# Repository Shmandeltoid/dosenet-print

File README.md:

# dosenet-print
for 3D print and PCB design files

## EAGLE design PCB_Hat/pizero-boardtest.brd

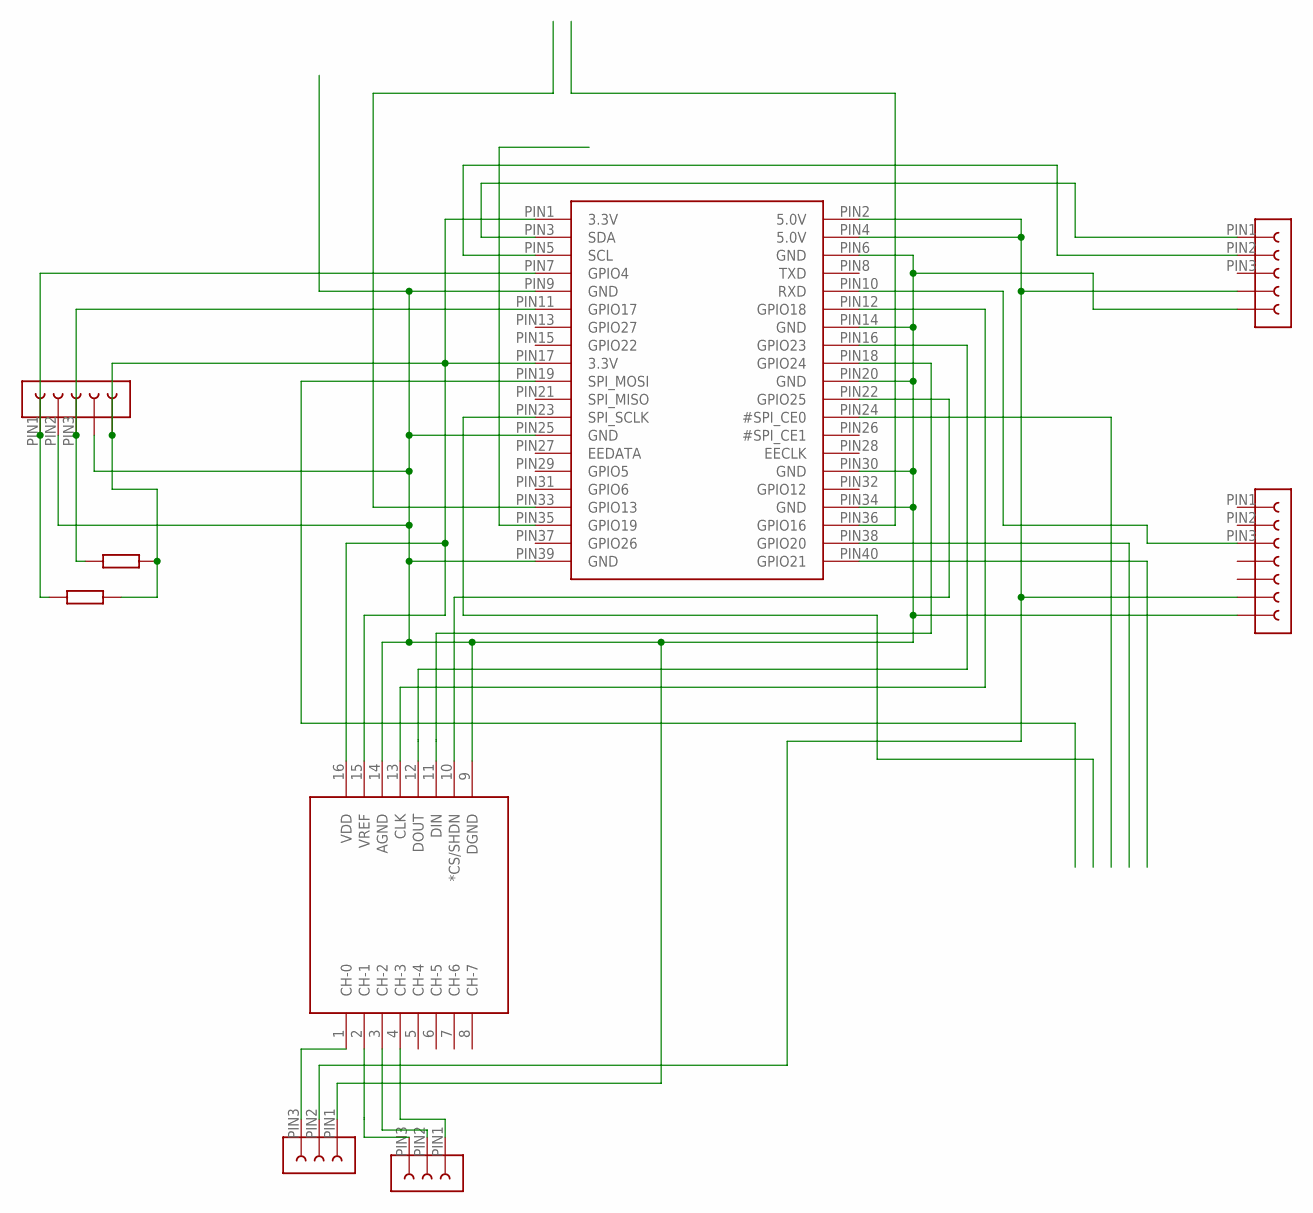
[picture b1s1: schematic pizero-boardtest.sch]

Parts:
ADC: ADC-CHIP; MCP3008-I/SL
U$1: RPI-CPU
U$2, U$6: 3PIN-HEADER
U$3, U$8: 5PIN-HEADER
U$4, U$5: 10KO-RESISTOR
U$9: 7PIN-HEADER

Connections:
3.3V: ADC.15 (VREF), ADC.16 (VDD), U$1.PIN1 (3.3V), U$1.PIN17 (3.3V), U$3.PIN5, U$4.P$2, U$5.P$2
5.0V: U$1.PIN2 (5.0V), U$1.PIN4 (5.0V), U$6.PIN2, U$8.PIN4, U$9.PIN6
CE0: U$1.PIN24 (#SPI_CE0)
GND: ADC.9 (DGND), ADC.14 (AGND), U$1.PIN6 (GND), U$1.PIN9 (GND), U$1.PIN14 (GND), U$1.PIN20 (GND), U$1.PIN25 (GND), U$1.PIN30 (GND), U$1.PIN34 (GND), U$1.PIN39 (GND), U$3.PIN2, U$3.PIN4, U$6.PIN1, U$8.PIN5, U$9.PIN7
GPIO4: U$1.PIN7 (GPIO4), U$3.PIN1, U$5.P$1
GPIO13: U$1.PIN33 (GPIO13)
GPIO16: U$1.PIN36 (GPIO16)
GPIO17: U$1.PIN11 (GPIO17), U$3.PIN3, U$4.P$1
GPIO18: ADC.13 (CLK), U$1.PIN12 (GPIO18)
GPIO19: U$1.PIN35 (GPIO19)
GPIO20: U$1.PIN38 (GPIO20)
GPIO21: U$1.PIN40 (GPIO21)
GPIO23: ADC.12 (DOUT), U$1.PIN16 (GPIO23)
GPIO24: ADC.11 (DIN), U$1.PIN18 (GPIO24)
GPIO25: ADC.10 (*CS/SHDN), U$1.PIN22 (GPIO25)
MOSI: U$1.PIN19 (SPI_MOSI)
unnamed: ADC.1 (CH-0), U$6.PIN3
unnamed: ADC.2 (CH-1), U$2.PIN3
unnamed: ADC.3 (CH-2), U$2.PIN2
unnamed: ADC.4 (CH-3), U$2.PIN1
RXD: U$1.PIN10 (RXD), U$9.PIN3
SCL: U$1.PIN5 (SCL), U$8.PIN2
SCLK: U$1.PIN23 (SPI_SCLK)
SDA: U$1.PIN3 (SDA), U$8.PIN1

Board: 2 copper layers, 9 parts (0 on the bottom side), 16 nets, no tracks yet.

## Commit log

2019-07-08 Create Summer19 Update
2019-07-24 Create miniPort
